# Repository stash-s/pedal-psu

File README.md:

Pedalboard PSU

Release 0.9

This version has PCB designed for JLCPCB.

PCB and brains of smart guitar pedal psu.

Four isolated lines, one with adjustable voltage and output resistance.

Adjustable source may be used to emulate depleted battery.

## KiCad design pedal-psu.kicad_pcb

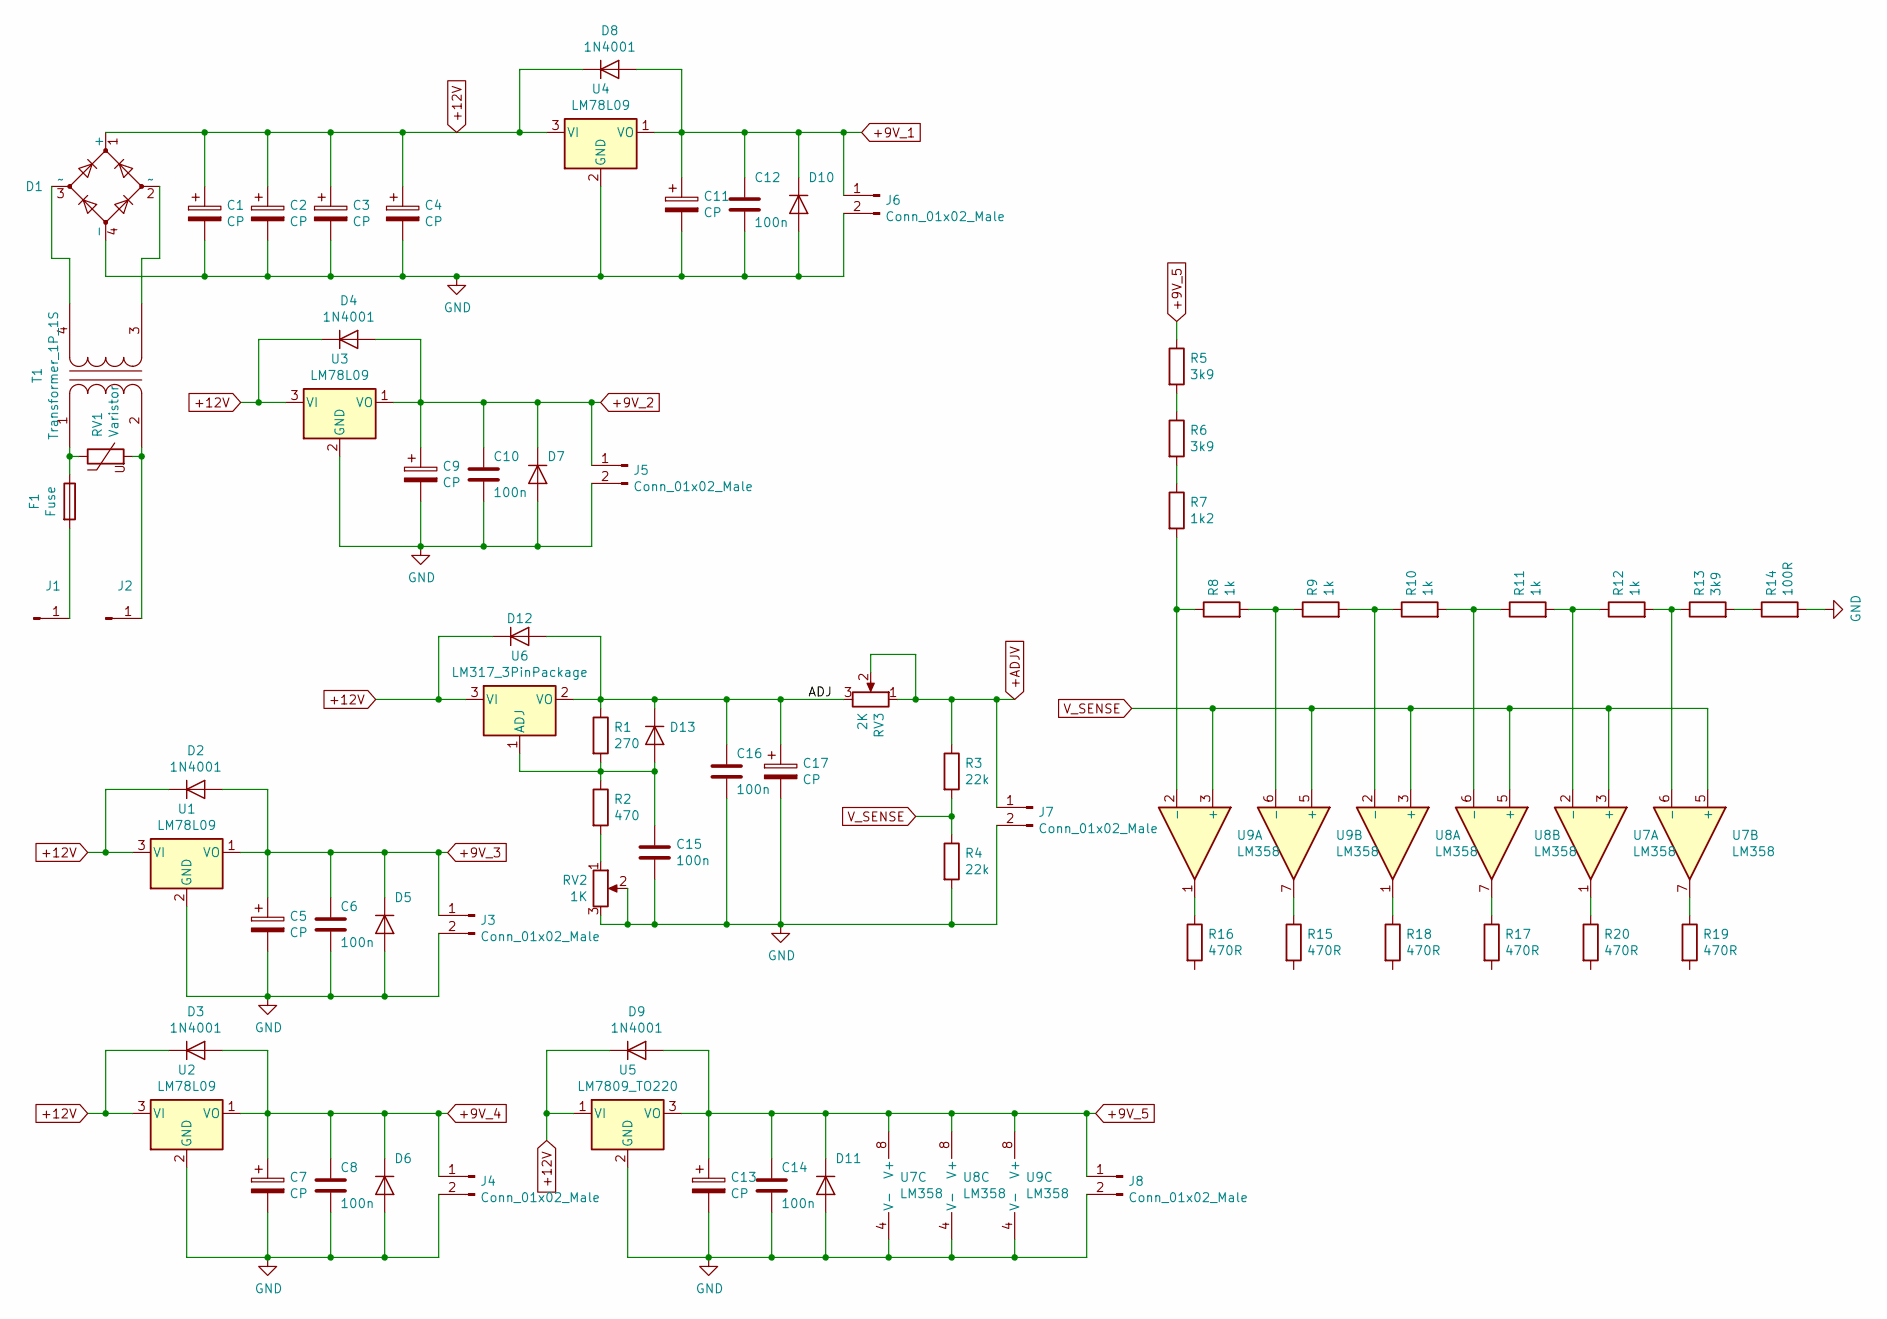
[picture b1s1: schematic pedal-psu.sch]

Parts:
C1, C2, C3, C4: CP; C_Radial_D10.0mm_H12.5mm_P5.00mm
C5, C7, C9, C11, C13, C17: CP; C_Radial_D6.3mm_H5.0mm_P2.50mm
C6, C8, C10, C12, C14, C15, C16: 100n; C_1210_3225Metric_Pad1.42x2.65mm_HandSolder
D1: D_Bridge_+AA-; Diode_Bridge_TELPOD_GB009_p4mm
D2, D3, D4, D5, D6, D7, D8, D9, D10, D11, D12, D13: 1N4001; D_DO-41_SOD81_P7.62mm_Horizontal
F1: Fuse; Fuse-PTF15
J1, J2: Conn_01x01_Male; Blade_3866B.68
J3, J4, J5, J6, J7, J8: Conn_01x02_Male; Molex_KK-254_AE-6410-02A_1x02_P2.54mm_Vertical
R1: 270; R_0805_2012Metric_Pad1.15x1.40mm_HandSolder
R2: 470; R_0805_2012Metric_Pad1.15x1.40mm_HandSolder
R3, R4: 22k; R_0805_2012Metric_Pad1.15x1.40mm_HandSolder
R5, R6, R13: 3k9; R_0805_2012Metric_Pad1.15x1.40mm_HandSolder
R7: 1k2; R_0805_2012Metric_Pad1.15x1.40mm_HandSolder
R8, R9, R10, R11, R12: 1k; R_0805_2012Metric_Pad1.15x1.40mm_HandSolder
R14: 100R; R_0805_2012Metric_Pad1.15x1.40mm_HandSolder
R15, R16, R17, R18, R19, R20: 470R; R_0805_2012Metric_Pad1.15x1.40mm_HandSolder
RV1: Varistor; RV_Disc_D15.5mm_W3.9mm_P7.5mm
RV2: 1K; Molex_KK-254_AE-6410-03A_1x03_P2.54mm_Vertical
RV3: 2K; Molex_KK-254_AE-6410-03A_1x03_P2.54mm_Vertical
T1: Transformer_1P_1S; Transformer_V42AJ
U1, U2, U3, U4: LM78L09; TO-92
U5: LM7809_TO220; TO220_Vertical_Radiator_L15mm_W10mm
U6: LM317_3PinPackage; TO220_Vertical_Radiator_L15mm_W10mm
U7, U8, U9: LM358; SOIC-8_3.9x4.9mm_P1.27mm

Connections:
+9V_1: C11.1, C12.1, D8.2 (A), D10.1 (K), J6.1, U4.1 (VO)
+9V_2: C9.1, C10.1, D4.2 (A), D7.1 (K), J5.1, U3.1 (VO)
+9V_3: C5.1, C6.1, D2.2 (A), D5.1 (K), J3.1, U1.1 (VO)
+9V_4: C7.1, C8.1, D3.2 (A), D6.1 (K), J4.1, U2.1 (VO)
+9V_5: C13.1, C14.1, D9.2 (A), D11.1 (K), J8.1, R5.1, U5.3 (VO), U7.8 (V+), U8.8 (V+), U9.8 (V+)
+12V: C1.1, C2.1, C3.1, C4.1, D1.1 (+), D2.1 (K), D3.1 (K), D4.1 (K), D8.1 (K), D9.1 (K), D12.1 (K), U1.3 (VI), U2.3 (VI), U3.3 (VI), U4.3 (VI), U5.1 (VI), U6.3 (VI)
+ADJV: J7.1, R3.1, RV3.1, RV3.2
/ADJ: C16.1, C17.1, D12.2 (A), D13.1 (K), R1.1, RV3.3, U6.2 (VO)
GND: C1.2, C2.2, C3.2, C4.2, C5.2, C6.2, C7.2, C8.2, C9.2, C10.2, C11.2, C12.2, C13.2, C14.2, C15.2, C16.2, C17.2, D1.4 (-), D5.2 (A), D6.2 (A), D7.2 (A), D10.2 (A), D11.2 (A), J3.2, J4.2, J5.2, J6.2, J7.2, J8.2, R4.2, R14.2, RV2.2, RV2.3, U1.2 (GND), U2.2 (GND), U3.2 (GND), U4.2 (GND), U5.2 (GND), U7.4 (V-), U8.4 (V-), U9.4 (V-); also elsewhere on the board
unnamed: C15.1, D13.2 (A), R1.2, R2.1, U6.1 (ADJ)
unnamed: D1.2 (~~), T1.3 (SA)
unnamed: D1.3 (~~), T1.4 (SB)
unnamed: F1.1, RV1.1, T1.1 (AA)
unnamed: F1.2, J1.1
unnamed: J2.1, RV1.2, T1.2 (AB)
unnamed 15: R19.2; also elsewhere on the board
unnamed 16: R20.2; also elsewhere on the board
unnamed 17: R17.2; also elsewhere on the board
unnamed 18: R18.2; also elsewhere on the board
unnamed 19: R15.2; also elsewhere on the board
unnamed 20: R16.2; also elsewhere on the board
unnamed: R2.2, RV2.1
unnamed: R5.2, R6.1
unnamed: R6.2, R7.1
unnamed: R7.2, R8.1, U9.2 (-)
unnamed: R8.2, R9.1, U9.6 (-)
unnamed: R9.2, R10.1, U8.2 (-)
unnamed: R10.2, R11.1, U8.6 (-)
unnamed: R11.2, R12.1, U7.2 (-)
unnamed: R12.2, R13.1, U7.6 (-)
unnamed: R13.2, R14.1
unnamed: R15.1, U9.7
unnamed: R16.1, U9.1
unnamed: R17.1, U8.7
unnamed: R18.1, U8.1
unnamed: R19.1, U7.7
unnamed: R20.1, U7.1
V_SENSE: R3.2, R4.1, U7.3 (+), U7.5 (+), U8.3 (+), U8.5 (+), U9.3 (+), U9.5 (+)

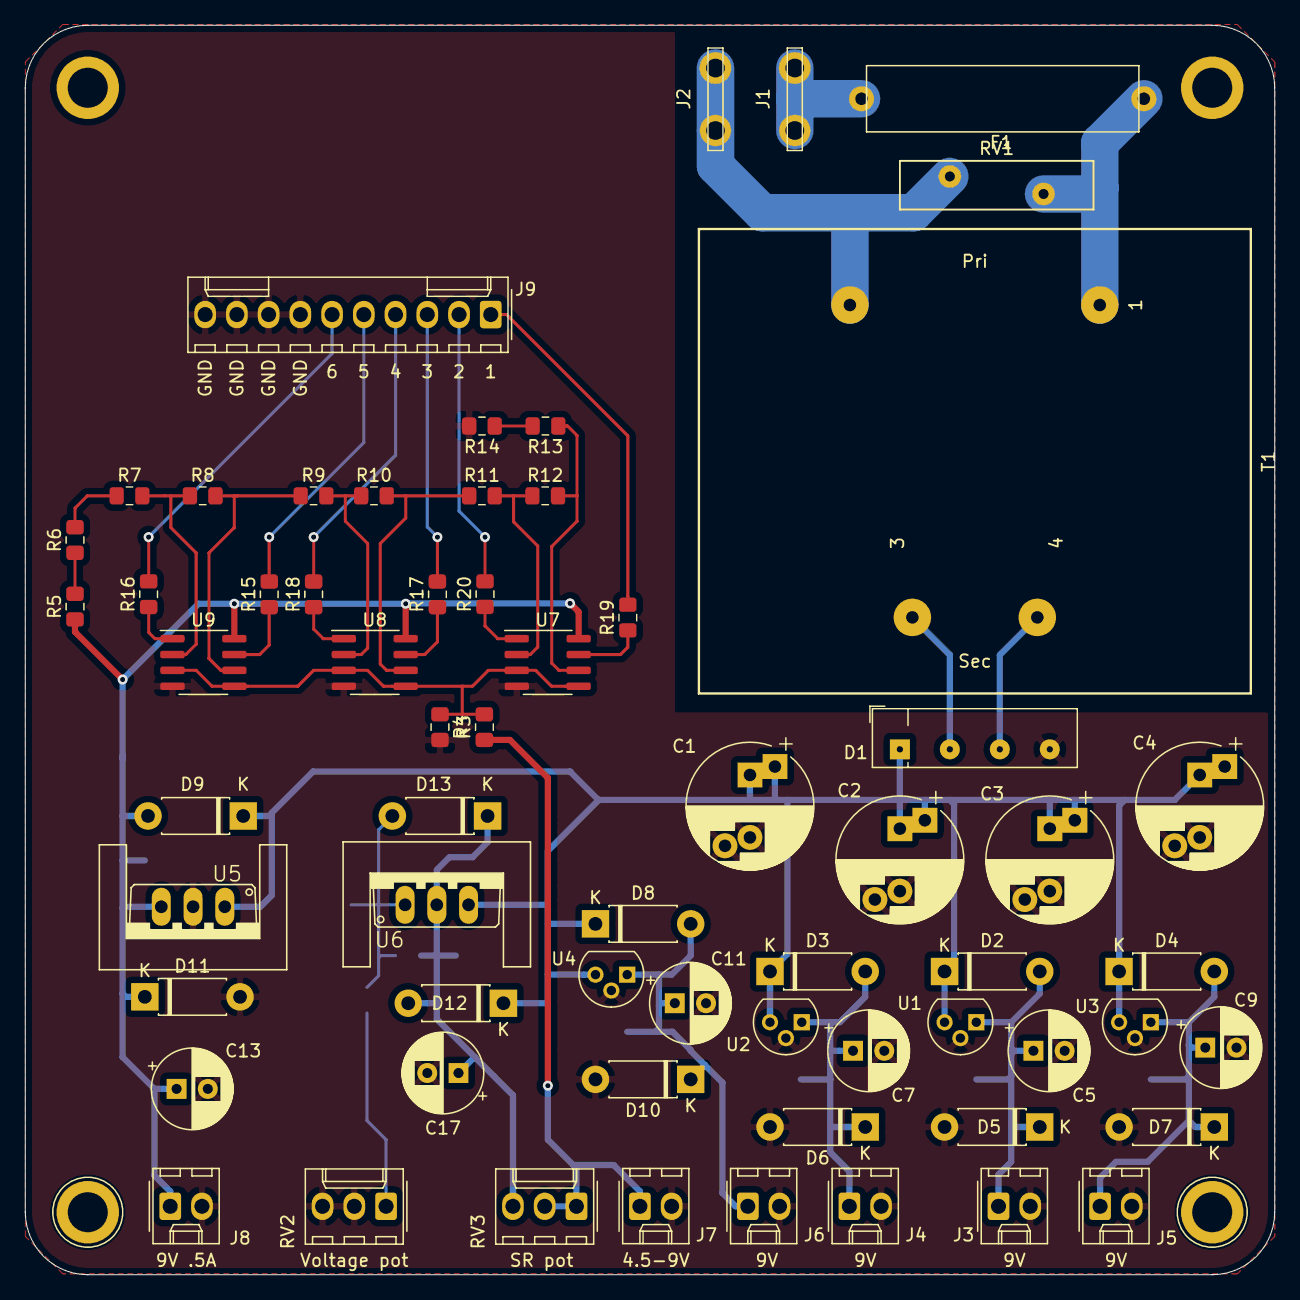
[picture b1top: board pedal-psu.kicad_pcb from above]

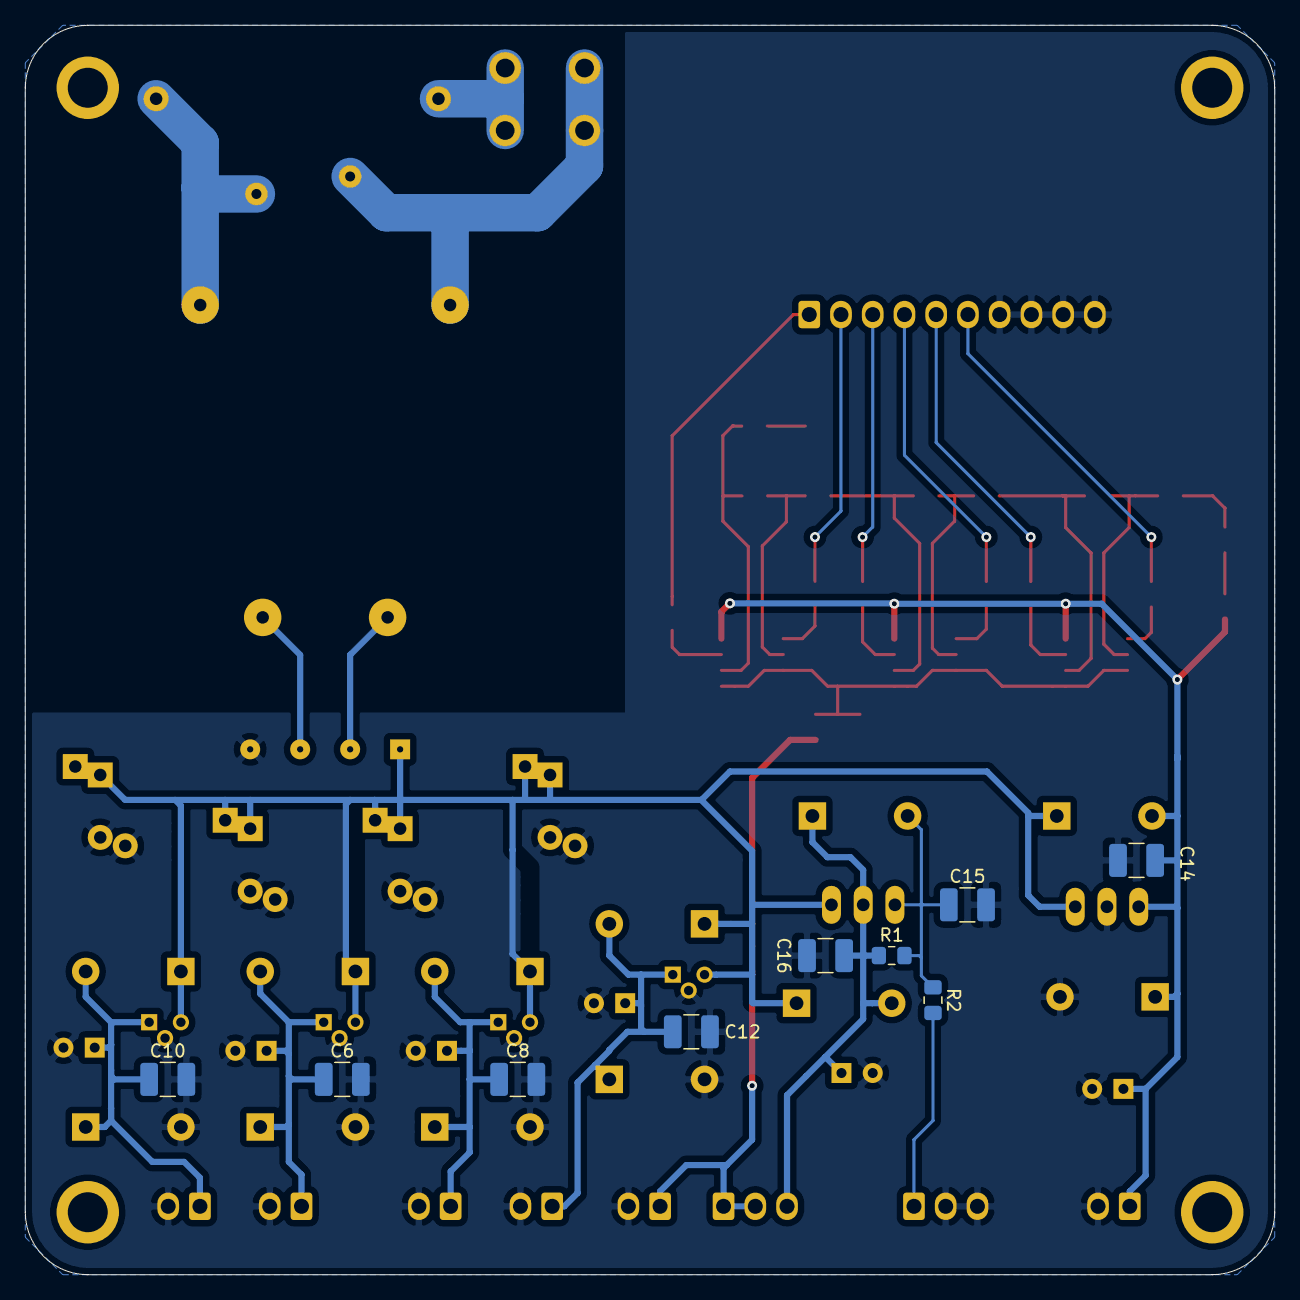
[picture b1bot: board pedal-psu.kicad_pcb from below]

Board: 2 copper layers, 100.0 x 100.0 mm, 73 parts (9 on the bottom side), 38 nets.

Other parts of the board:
J9: Conn_01x10_Male; Molex_KK-254_AE-6410-10A_1x10_P2.54mm_Vertical

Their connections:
GND: J9.7, J9.8, J9.9, J9.10; also elsewhere on the board
unnamed 15: J9.1; also elsewhere on the board
unnamed 16: J9.2; also elsewhere on the board
unnamed 17: J9.3; also elsewhere on the board
unnamed 18: J9.4; also elsewhere on the board
unnamed 19: J9.5; also elsewhere on the board
unnamed 20: J9.6; also elsewhere on the board

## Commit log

2019-01-04 Initial commit.
2019-01-04 Commented purpose in README.md
2019-01-04 Complete schematic, moving on to PCB design.
2019-01-07 Moved things around on PCB
2019-01-15 Moving Op-Amp into place.
2019-11-10 Removed 2nd trafo.
2019-11-11 Complete PCB ready for hand etching.
2019-11-11 Version bumped.
2019-11-11 Bumped release version.
2019-11-11 Machine version of PCB created.
2019-11-11 Version bump and minor cleanup.
